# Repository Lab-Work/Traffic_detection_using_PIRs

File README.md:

# Traffic_detection_using_PIRs
Yanning Li, Christopher Chen, Fangyu Wu, December, 2017

## 1) Overview
This repository contains the source code developed for traffic detection and vehicle speed estimation using PIR sensors. This results are reported in a journal paper *"Traffic detection via energy efficient passive infrared sensing"* by Yanning Li, Christopher Chen, Fangyu Wu, Christian Claudel, and Daniel Work, which was submitted to *IEEE Transactions on Intelligent Transportation Systems*.

## 2) License

This software is licensed under the *University of Illinois/NCSA Open Source License*:

**Copyright (c) 2017 The Board of Trustees of the University of Illinois. All rights reserved**

**Developed by: Department of Civil and Environmental Engineering University of Illinois at Urbana-Champaign**

Permission is hereby granted, free of charge, to any person obtaining a copy of this software and associated documentation files (the "Software"), to deal with the Software without restriction, including without limitation the rights to use, copy, modify, merge, publish, distribute, sublicense, and/or sell copies of the Software, and to permit persons to whom the Software is furnished to do so, subject to the following conditions: Redistributions of source code must retain the above copyright notice, this list of conditions and the following disclaimers. Redistributions in binary form must reproduce the above copyright notice, this list of conditions and the following disclaimers in the documentation and/or other materials provided with the distribution. Neither the names of the Department of Civil and Environmental Engineering, the University of Illinois at Urbana-Champaign, nor the names of its contributors may be used to endorse or promote products derived from this Software without specific prior written permission.

THE SOFTWARE IS PROVIDED "AS IS", WITHOUT WARRANTY OF ANY KIND, EXPRESS OR IMPLIED, INCLUDING BUT NOT LIMITED TO THE WARRANTIES OF MERCHANTABILITY, FITNESS FOR A PARTICULAR PURPOSE AND NONINFRINGEMENT. IN NO EVENT SHALL THE CONTRIBUTORS OR COPYRIGHT HOLDERS BE LIABLE FOR ANY CLAIM, DAMAGES OR OTHER LIABILITY, WHETHER IN AN ACTION OF CONTRACT, TORT OR OTHERWISE, ARISING FROM, OUT OF OR IN CONNECTION WITH THE SOFTWARE OR THE USE OR OTHER DEALINGS WITH THE SOFTWARE.

## 3) Structure

This repository is devided to three folders/repositories, i.e., `/Detection platform/`, `ITS2017_Validation`, and `Traffic_Sensors_Algorithms`, primarily developed by Christopher Chen, Fangyu Wu, and Yanning Li, respectively.  

- `Detection platform`: the source code for the hardware traffic sensing nodes, i.e., firmware and sensor libraries. 

- `ITS2017_Validation`: the repository for generating the true traffic detection and speed using videos and computer vision. The true detection and speeds are used for evaluating the performance of the energy efficient PIR sensors for traffic detection.

- `Traffic_Sensors_Algorithms`: the repository that contains the source code for processing the PIR sensor data for traffic detection and speed estimation. 
	
Please refer to the readme file in each folder or repository for how to use the code.

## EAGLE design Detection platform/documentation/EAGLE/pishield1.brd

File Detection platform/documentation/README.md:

#  /coordinator

## ./EAGLE

This folder contains the schematics and layout for the Raspberry Pi hat interface board.

## ./mount_plate.pdf

This is the pdf for laser cutting the acrylic tripod mount plates.

## ./pir_mount.stl

This is the CAD file for the PIR and ultrasonic mounts. All four components for assembly can be found here.

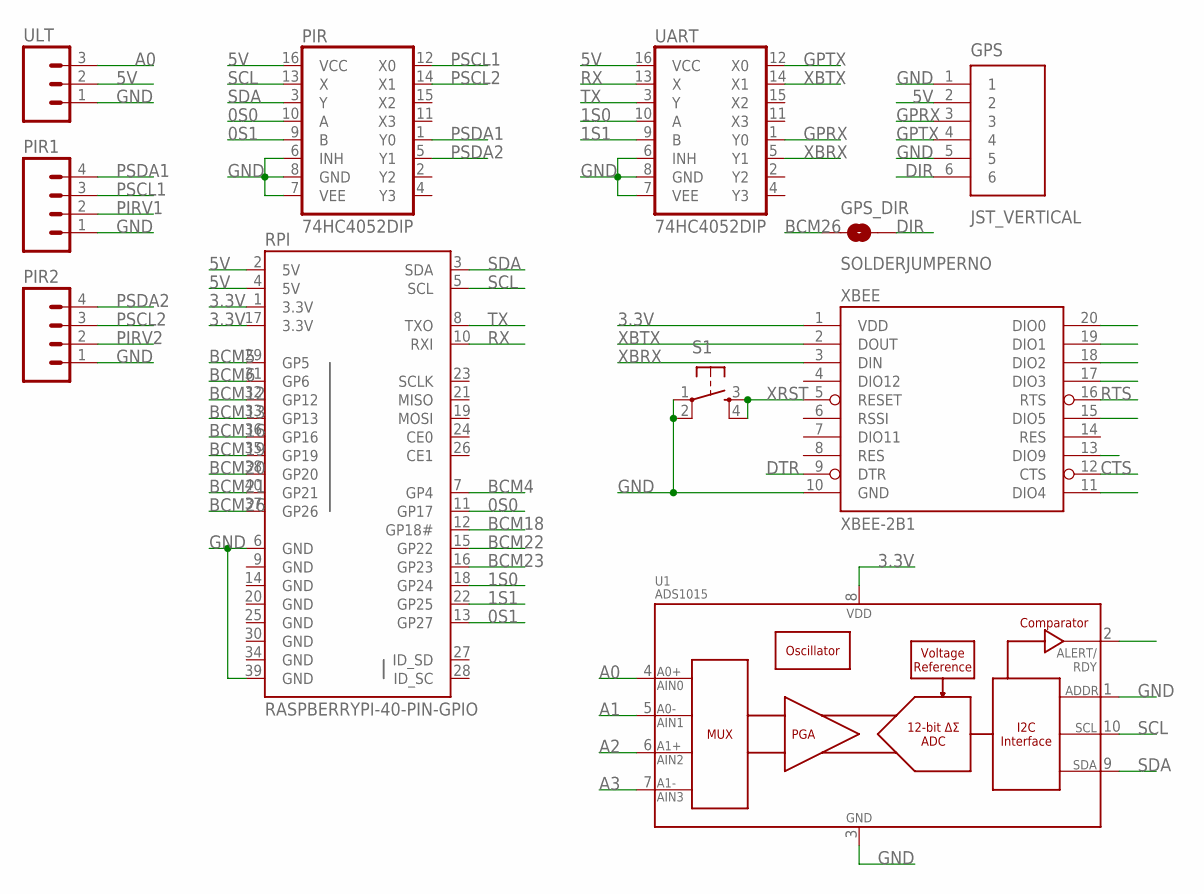
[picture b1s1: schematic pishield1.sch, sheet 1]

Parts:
GPS: JST_VERTICAL; JST-6-SMD-VERT-1.0MM
GPS_DIR: SOLDERJUMPERNO; SJ_2S-NO
PIR: 74HC4052DIP; DIL16
PIR1, PIR2: M04PTH; 1X04
RPI: RASPBERRYPI-40-PIN-GPIO; 2X20-SHROUDED
S1: TAC_SWITCHPTH; TACTILE-PTH
U1: ADS1015; MSOP10
UART: 74HC4052DIP; DIL16
ULT: M03PTH; 1X03
XBEE: XBEE-2B1; XBEE-1

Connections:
0S0: PIR.10 (A), RPI.11 (GP17)
0S1: PIR.9 (B), RPI.13 (GP27)
1S0: RPI.18 (GP24), UART.10 (A)
1S1: RPI.22 (GP25), UART.9 (B)
3.3V: RPI.1 (3.3V), RPI.17 (3.3V), U1.8 (VDD), XBEE.1 (VDD)
5V: GPS.2, PIR.16 (VCC), RPI.2 (5V), RPI.4 (5V), UART.16 (VCC), ULT.2; also elsewhere on the board
A0: U1.4 (AIN0), ULT.3
A1: U1.5 (AIN1)
A2: U1.6 (AIN2)
A3: U1.7 (AIN3)
BCM4: RPI.7 (GP4)
BCM5: RPI.29 (GP5)
BCM6: RPI.31 (GP6)
BCM12: RPI.32 (GP12); also elsewhere on the board
BCM13: RPI.33 (GP13); also elsewhere on the board
BCM16: RPI.36 (GP16); also elsewhere on the board
BCM18: RPI.12 (GP18#)
BCM19: RPI.35 (GP19); also elsewhere on the board
BCM20: RPI.38 (GP20); also elsewhere on the board
BCM21: RPI.40 (GP21); also elsewhere on the board
BCM22: RPI.15 (GP22)
BCM23: RPI.16 (GP23)
BCM26: GPS_DIR.1, RPI.37 (GP26)
CTS: XBEE.12 (CTS)
DIR: GPS.6, GPS_DIR.2
DTR: XBEE.9 (DTR)
GND: GPS.1, GPS.5, PIR.6 (INH), PIR.7 (VEE), PIR.8 (GND), PIR1.1, PIR2.1, RPI.6 (GND), RPI.9 (GND), RPI.14 (GND), RPI.20 (GND), RPI.25 (GND), RPI.30 (GND), RPI.34 (GND), RPI.39 (GND), S1.1, S1.2, U1.1 (ADDR), U1.3 (VSS), UART.6 (INH), UART.7 (VEE), UART.8 (GND), ULT.1, XBEE.10 (GND); also elsewhere on the board
GPRX: GPS.3, UART.1 (Y0)
GPTX: GPS.4, UART.12 (X0)
PIRV1: PIR1.2; also elsewhere on the board
PIRV2: PIR2.2; also elsewhere on the board
PSCL1: PIR.12 (X0), PIR1.3
PSCL2: PIR.14 (X1), PIR2.3
PSDA1: PIR.1 (Y0), PIR1.4
PSDA2: PIR.5 (Y1), PIR2.4
RTS: XBEE.16 (RTS)
RX: RPI.10 (RXI), UART.13 (X)
SCL: PIR.13 (X), RPI.5 (SCL), U1.10 (SCL)
SDA: PIR.3 (Y), RPI.3 (SDA), U1.9 (SDA)
TX: RPI.8 (TXO), UART.3 (Y)
XBRX: UART.5 (Y1), XBEE.3 (DIN)
XBTX: UART.14 (X1), XBEE.2 (DOUT)
XRST: S1.3, S1.4, XBEE.5 (RESET)

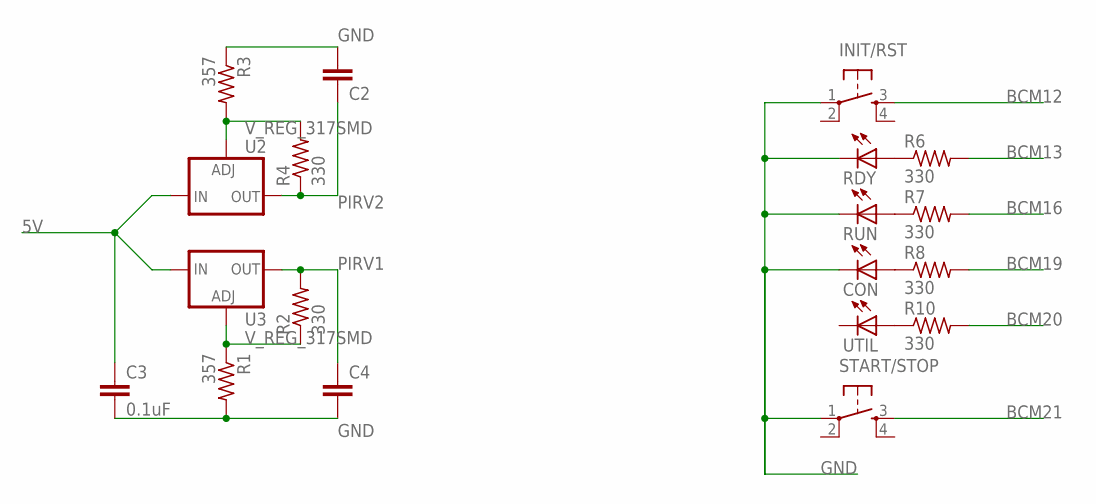
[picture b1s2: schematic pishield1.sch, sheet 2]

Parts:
C2, C4: CAPPTH; CAP-PTH-SMALL
C3: 0.1uF; CAP-PTH-SMALL
CON: LEDSML1206; SML1206
INIT/RST: TAC_SWITCHPTH; TACTILE-PTH
R1, R3: 357; M0805
R2, R4, R6, R7, R8, R10: 330; M0805
RDY: LEDSML1206; SML1206
RUN: LEDSML1206; SML1206
START/STOP: TAC_SWITCHPTH; TACTILE-PTH
U2, U3: V_REG_317SMD; SOT223
UTIL: LEDSML1206; SML1206

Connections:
5V: C3.1, U2.3 (IN), U3.3 (IN); also elsewhere on the board
BCM12: INIT/RST.3; also elsewhere on the board
BCM13: R6.2; also elsewhere on the board
BCM16: R7.2; also elsewhere on the board
BCM19: R8.2; also elsewhere on the board
BCM20: R10.2; also elsewhere on the board
BCM21: START/STOP.3; also elsewhere on the board
GND: C2.2, C3.2, C4.2, CON.C, INIT/RST.1, R1.2, R3.1, RDY.C, RUN.C, START/STOP.1; also elsewhere on the board
unnamed: R3.2, R4.2, U2.1 (ADJ)
unnamed: R6.1, RDY.A
unnamed: R7.1, RUN.A
unnamed: CON.A, R8.1
unnamed: R10.1, UTIL.A
unnamed: R1.1, R2.1, U3.1 (ADJ)
PIRV1: C4.1, R2.2, U3.2 (OUT); also elsewhere on the board
PIRV2: C2.1, R4.1, U2.2 (OUT); also elsewhere on the board

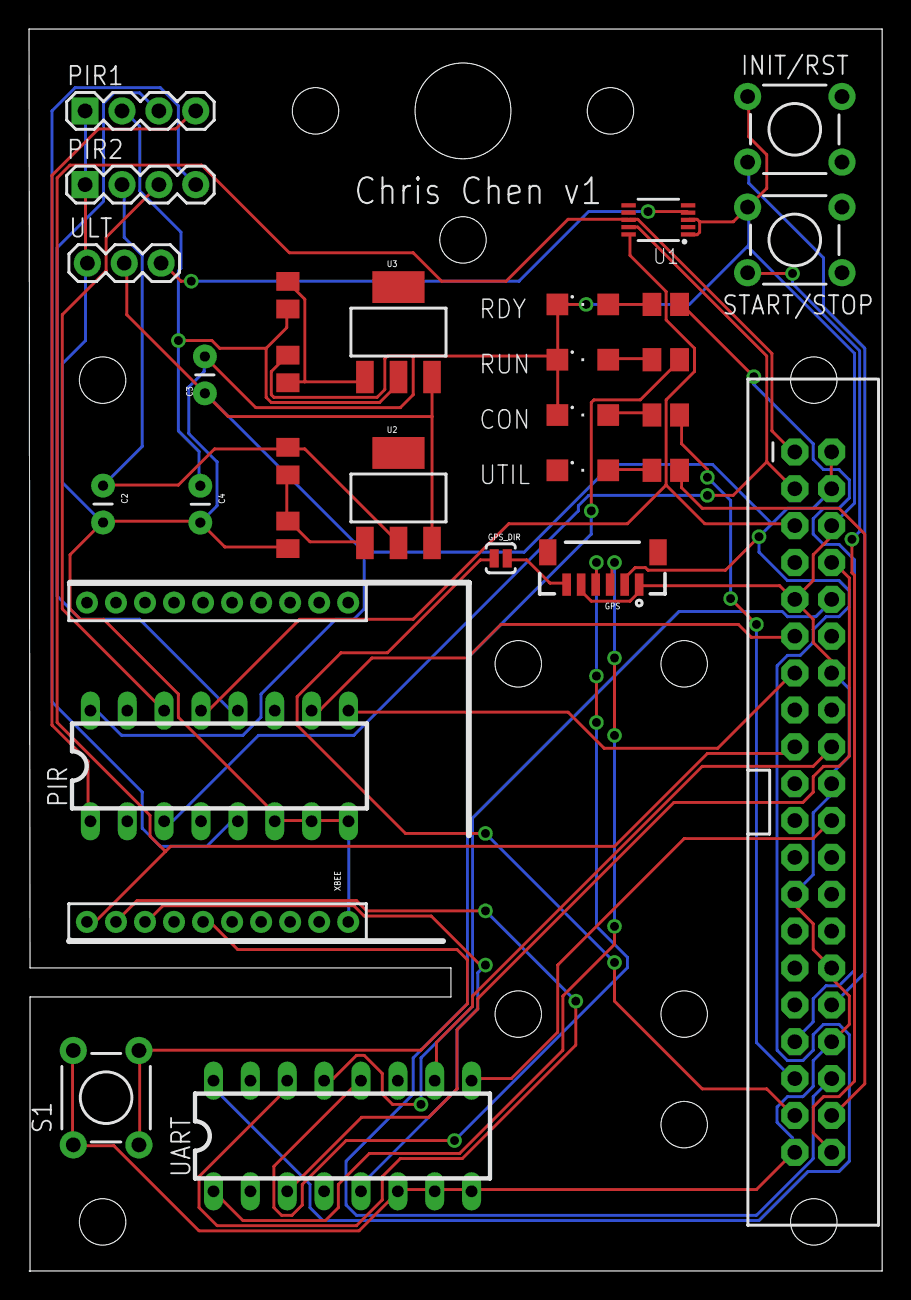
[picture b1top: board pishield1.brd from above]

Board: 2 copper layers, 58.8 x 85.6 mm, 30 parts (0 on the bottom side), 37 nets.

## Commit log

2017-06-28 initial commit
    transfer from Sensor_Network repo
2017-06-30 reformatted
2017-07-01 removed some files
2017-07-01 updated
    updated
2017-07-08 cleanup
2017-08-15 added a few files
2017-08-15 A few small changes
2017-08-15 Formatting
2017-08-15 readme
2017-12-29 Added submodules for traffic sensor algorithms and the video validation.

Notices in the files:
parts and their libraries:
SparkFun-Connectors: Licensing: Creative Commons ShareAlike 4.0 International - https://creativecommons.org/licenses/by-sa/4.0
